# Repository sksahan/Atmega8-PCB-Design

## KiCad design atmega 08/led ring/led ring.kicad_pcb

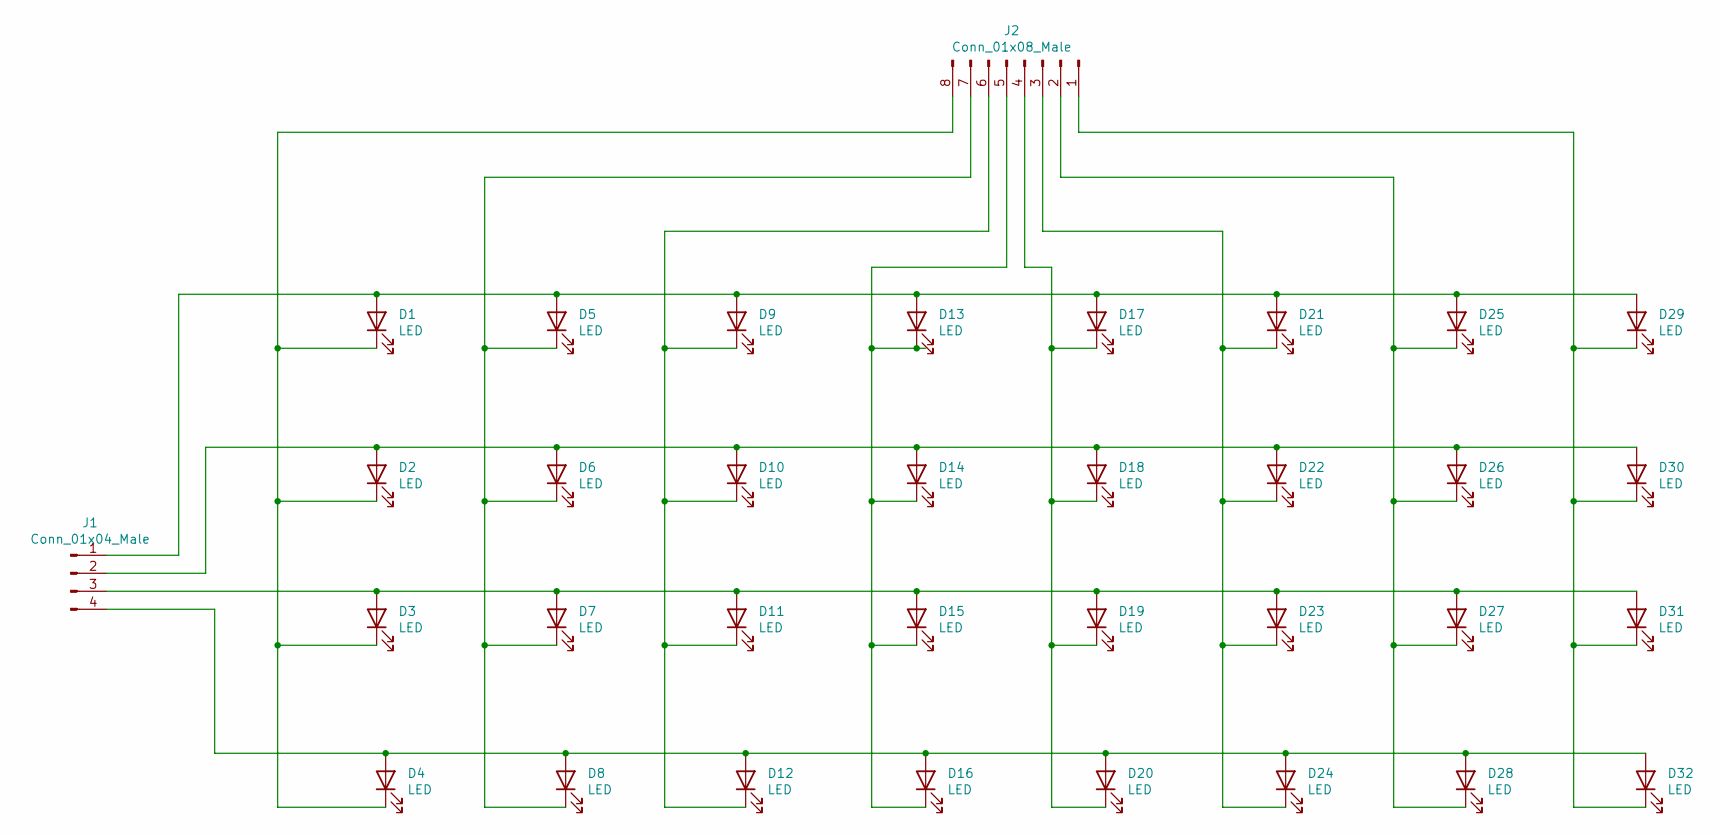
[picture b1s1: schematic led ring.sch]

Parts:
D1, D2, D3, D4, D5, D6, D7, D8, D9, D10, D11, D12, D13, D14, D15, D16, D17, D18, D19, D20, D21, D22, D23, D24, D25, D26, D27, D28, D29, D30, D31, D32: LED; LED_D5.0mm
J1: Conn_01x04_Male; PinSocket_1x04_P2.54mm_Vertical
J2: Conn_01x08_Male; PinSocket_1x08_P2.54mm_Vertical

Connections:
unnamed: D1.1 (K), D2.1 (K), D3.1 (K), D4.1 (K), J2.8
unnamed: D1.2 (A), D5.2 (A), D9.2 (A), D13.2 (A), D17.2 (A), D21.2 (A), D25.2 (A), D29.2 (A), J1.1
unnamed: D5.1 (K), D6.1 (K), D7.1 (K), D8.1 (K), J2.7
unnamed: D9.1 (K), D10.1 (K), D11.1 (K), D12.1 (K), J2.6
unnamed: D2.2 (A), D6.2 (A), D10.2 (A), D14.2 (A), D18.2 (A), D22.2 (A), D26.2 (A), D30.2 (A), J1.2
unnamed: D3.2 (A), D7.2 (A), D11.2 (A), D15.2 (A), D19.2 (A), D23.2 (A), D27.2 (A), D31.2 (A), J1.3
unnamed: D4.2 (A), D8.2 (A), D12.2 (A), D16.2 (A), D20.2 (A), D24.2 (A), D28.2 (A), D32.2 (A), J1.4
unnamed: D13.1 (K), D14.1 (K), D15.1 (K), D16.1 (K), J2.5
unnamed: D17.1 (K), D18.1 (K), D19.1 (K), D20.1 (K), J2.4
unnamed: D21.1 (K), D22.1 (K), D23.1 (K), D24.1 (K), J2.3
unnamed: D25.1 (K), D26.1 (K), D27.1 (K), D28.1 (K), J2.2
unnamed: D29.1 (K), D30.1 (K), D31.1 (K), D32.1 (K), J2.1

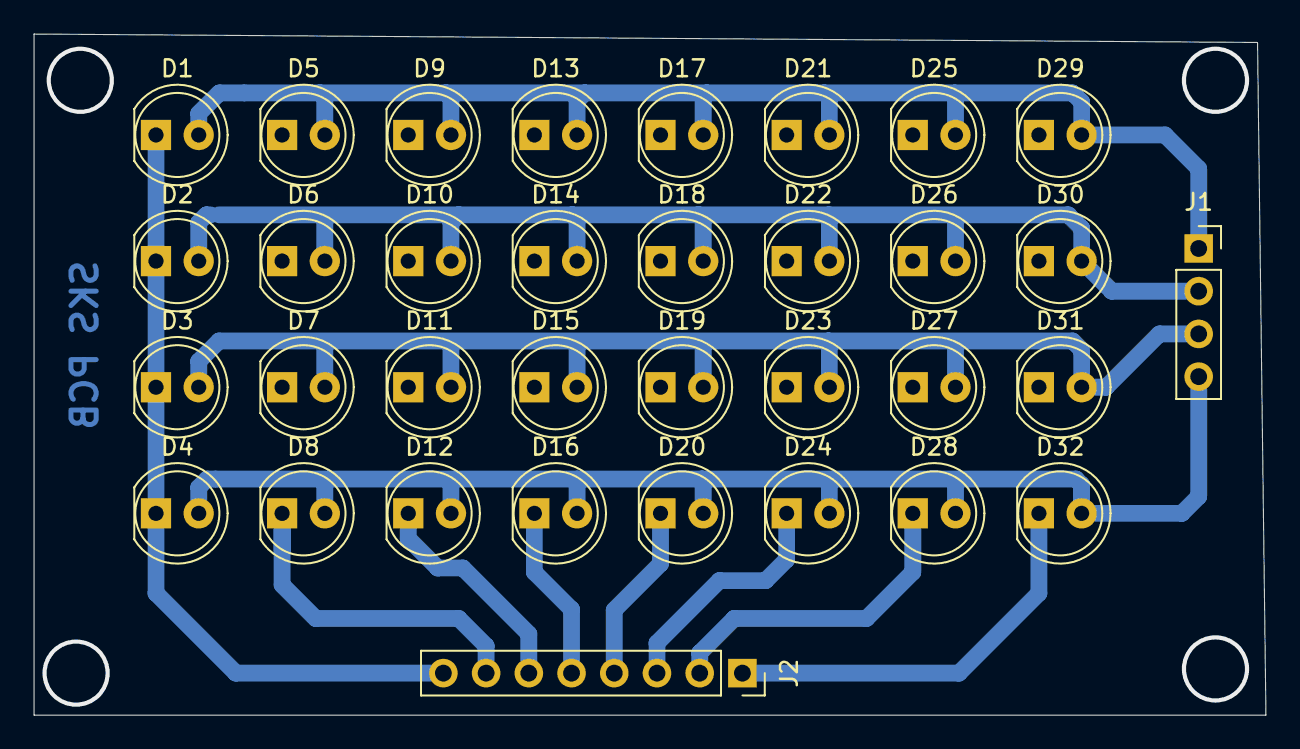
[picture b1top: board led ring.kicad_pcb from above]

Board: 2 copper layers, 73.2 x 40.5 mm, 34 parts (0 on the bottom side), 12 nets.

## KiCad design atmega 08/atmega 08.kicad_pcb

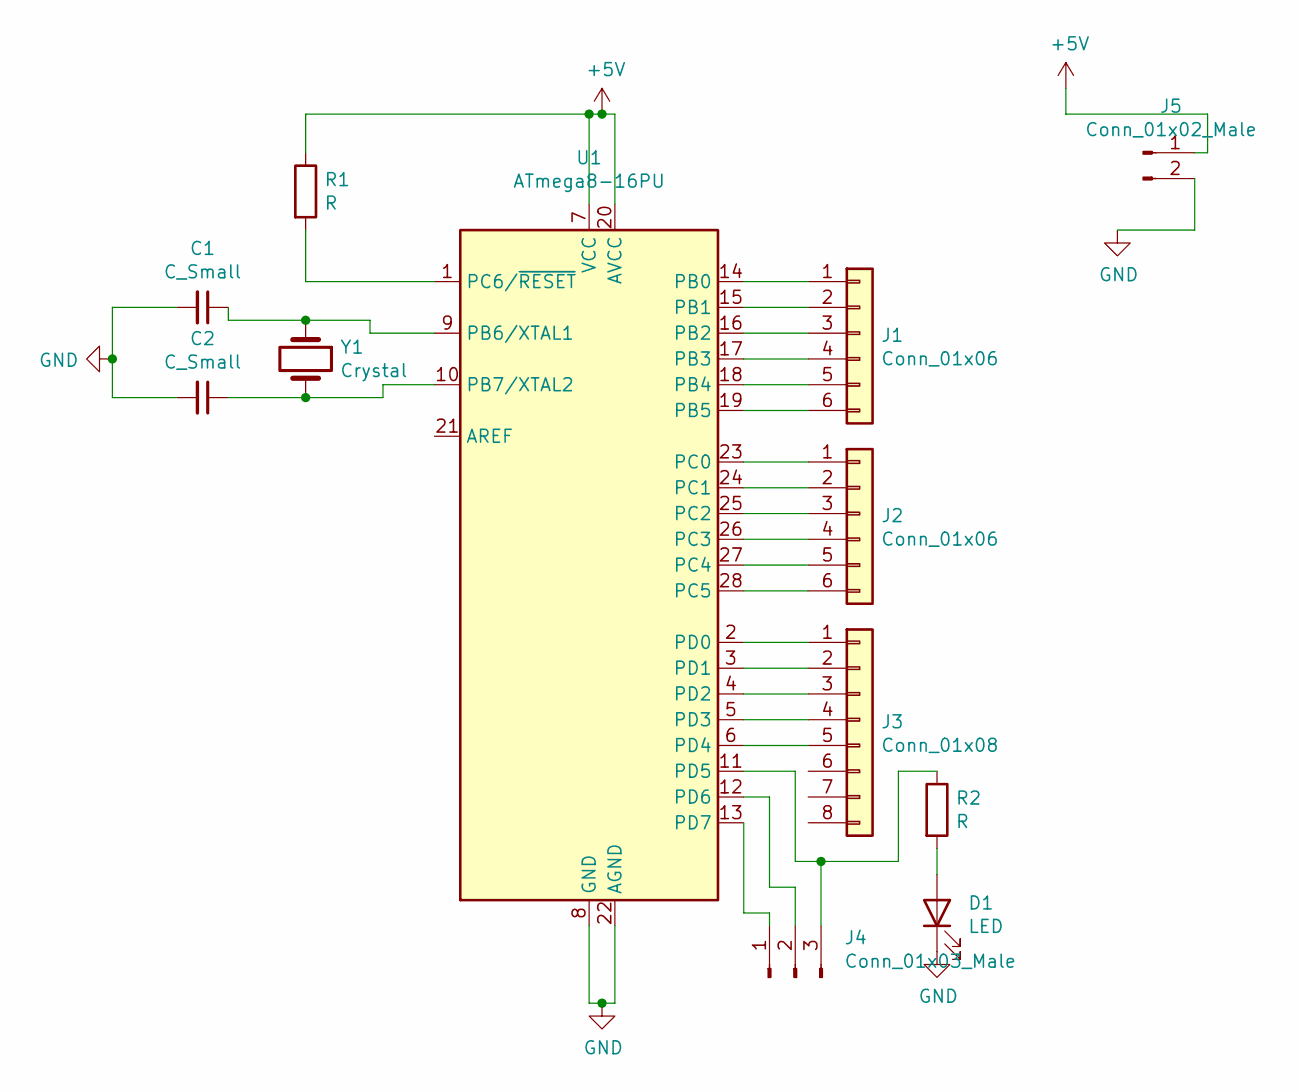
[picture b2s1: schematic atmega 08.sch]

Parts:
C1, C2: C_Small; CP_Radial_D4.0mm_P1.50mm
D1: LED; LED_D5.0mm
J1, J2: Conn_01x06; PinHeader_1x06_P2.54mm_Vertical
J3: Conn_01x08; PinHeader_1x08_P2.54mm_Vertical
J4: Conn_01x03_Male; PinHeader_1x03_P2.54mm_Vertical
J5: Conn_01x02_Male; PinHeader_1x02_P2.54mm_Vertical
R1, R2: R; R_Axial_DIN0204_L3.6mm_D1.6mm_P5.08mm_Vertical
U1: ATmega8-16PU; DIP-28_W7.62mm
Y1: Crystal; Crystal_HC18-U_Vertical

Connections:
+5V: J5.1, R1.1, U1.7 (VCC), U1.20 (AVCC)
GND: C1.2, C2.2, D1.1 (K), J5.2, U1.8 (GND), U1.22 (AGND)
unnamed: C1.1, U1.9 (PB6/XTAL1), Y1.1
unnamed: C2.1, U1.10 (PB7/XTAL2), Y1.2
unnamed: D1.2 (A), R2.2
unnamed: J1.1, U1.14 (PB0)
unnamed: J1.2, U1.15 (PB1)
unnamed: J1.3, U1.16 (PB2)
unnamed: J1.4, U1.17 (PB3)
unnamed: J1.5, U1.18 (PB4)
unnamed: J1.6, U1.19 (PB5)
unnamed: J2.1, U1.23 (PC0)
unnamed: J2.2, U1.24 (PC1)
unnamed: J2.3, U1.25 (PC2)
unnamed: J2.4, U1.26 (PC3)
unnamed: J2.5, U1.27 (PC4)
unnamed: J2.6, U1.28 (PC5)
unnamed: J3.1, U1.2 (PD0)
unnamed: J3.2, U1.3 (PD1)
unnamed: J3.3, U1.4 (PD2)
unnamed: J3.4, U1.5 (PD3)
unnamed: J3.5, U1.6 (PD4)
unnamed: J4.1, U1.13 (PD7)
unnamed: J4.2, U1.12 (PD6)
unnamed: J4.3, R2.1, U1.11 (PD5)
unnamed: R1.2, U1.1 (PC6/~RESET)

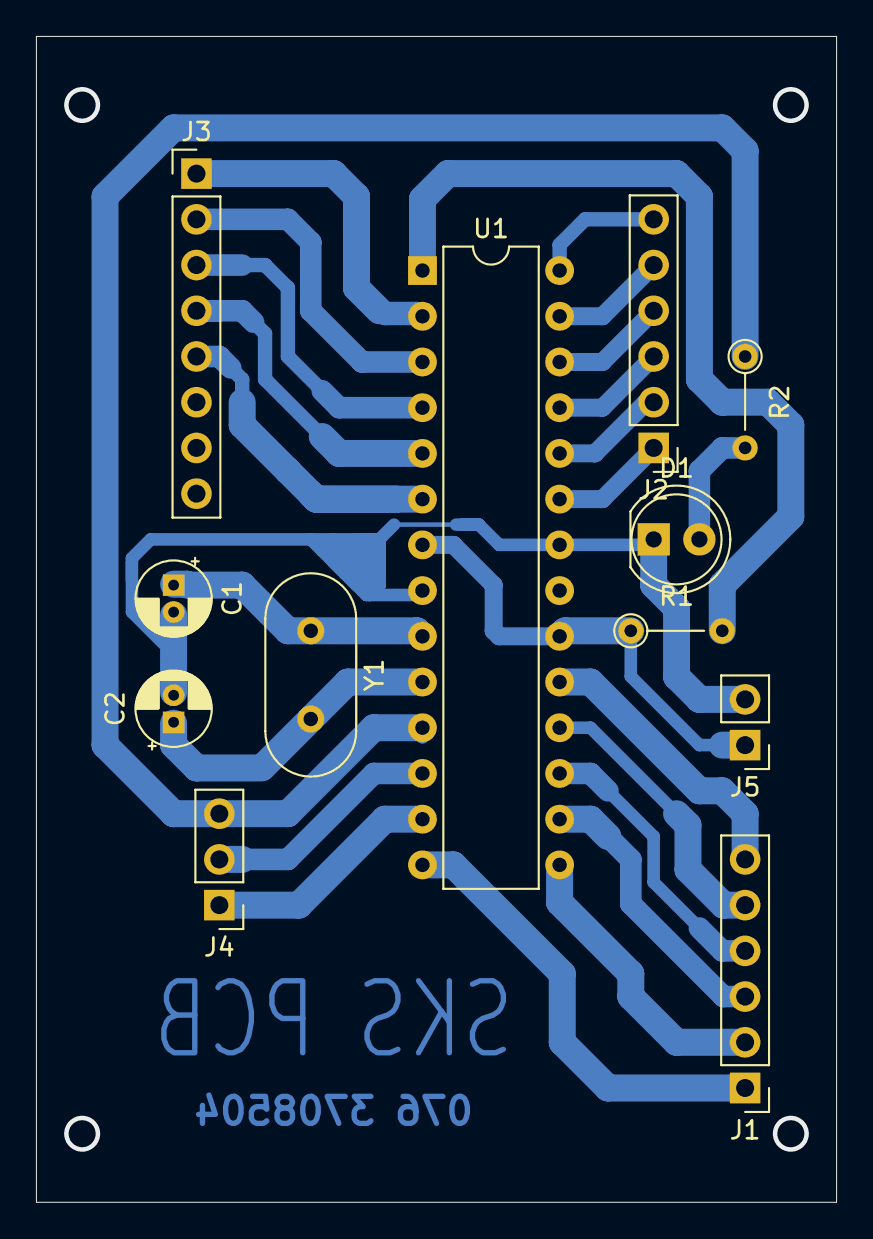
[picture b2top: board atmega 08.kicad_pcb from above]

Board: 2 copper layers, 44.5 x 64.8 mm, 12 parts (0 on the bottom side), 26 nets.
